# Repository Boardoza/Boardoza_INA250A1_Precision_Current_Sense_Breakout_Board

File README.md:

# Boardoza INA250A1 High Precision Current Sense Breakout Board

The **Boardoza INA250A1** is a high-precision **current-sense breakout board** based on the **Texas Instruments INA250A1** integrated current shunt monitor. It combines a precision differential amplifier and an internal **2 mΩ shunt resistor**, enabling accurate current measurements with minimal external components.

This breakout board is suitable for both **unidirectional and bidirectional current sensing** applications. Making it ideal for **power monitoring, energy management, motor control, battery systems, and industrial applications** where accurate current measurement is critical.

## [Click here to purchase!](https://www.ozdisan.com/ureticiler/boardoza)
| Front Side | Back Side |
|:---:|:---:|
|  |  |

---

## Key Features

- **High-Precision Current Shunt Monitor:** Enables accurate current measurement.  
- **Integrated 2 mΩ Precision Shunt Resistor:** Eliminates the need for an external shunt resistor.
- **Bidirectional Measurement Support:** Supports both unidirectional and bidirectional current measurement.
- **Wide Supply Voltage Range:** Compatible with wide supply voltage levels (**2.7 Vdc to 36 Vdc**).   
- **Analog Voltage Output:** Allows easy interfacing with ADCs and microcontrollers.
- **Low Power Consumption:** Suitable for energy-efficient applications.
- **Adjustable Reference Voltage (REF):** Enables output offset adjustment for measurement flexibility.  
- **Maximum Input Current Capability:** Supports current measurement up to **15 A (max)**.  

---

## Technical Specifications

**Model:** INA250A1  
**Manufacturer:** Boardoza  
**Manufacturer IC:** Texas Instruments  
**Functions:** Precision current sensing  
**Supply Voltage:** 2.7 V – 36 V  
**Maximum Input Current:** 15 A (Max)  
**Shunt Resistance:** 2 mΩ (internal)  
**Gain:** 200 mV/A  
**Output Type:** Analog voltage  
**Measurement Type:** Unidirectional / Bidirectional  
**Operating Temperature:** -40 °C to +125 °C  
**Board Dimensions:** 40 mm × 40 mm

---

## Board Pinout

### **( J1 ) Signal Connector**

| Pin Number | Pin Name | Description |
| :---: | :---: | --- |
| 1 | VS | Device power supply (2.7 V – 36 V) |
| 2 | REF | Reference voltage input |
| 3 | OUT | Analog output voltage |
| 4 | GND | Ground |

### **( J2 ) Current Path Connector**

| Pin Number | Pin Name | Description |
| :---: | :---: | --- |
| 1 | IN+ | Current sense input (supply side) |
| 2 | IN- | Current sense input (load side) |

---

## Board Dimensions

---

## Step Files

[Boardoza INA250A1.step](./assets/INA250A1%20Step.step)

---

## Datasheet

[INA250 Datasheet.pdf](./assets/INA250A1%20Datasheet.pdf)

---

## Version History

- V1.0.0 – Initial Release

---

## Support

- If you have any questions or need support, please contact **<support@boardoza.com>**

---

## **License**

This repository contains both hardware and software components:

### **Hardware Design**

[![CC BY-SA 4.0][cc-by-sa-shield]][cc-by-sa]

All hardware design files are licensed under [Creative Commons Attribution-ShareAlike 4.0 International License][cc-by-sa].

[cc-by-sa]: http://creativecommons.org/licenses/by-sa/4.0/
[cc-by-sa-shield]: https://img.shields.io/badge/License-CC%20BY--SA%204.0-lightgrey.svg

### **Software/Firmware**

[![BSD-3-Clause][bsd-shield]][bsd]

All software and firmware are licensed under [BSD 3-Clause License][bsd].

[bsd]: https://opensource.org/licenses/BSD-3-Clause
[bsd-shield]: https://img.shields.io/badge/License-BSD%203--Clause-blue.svg

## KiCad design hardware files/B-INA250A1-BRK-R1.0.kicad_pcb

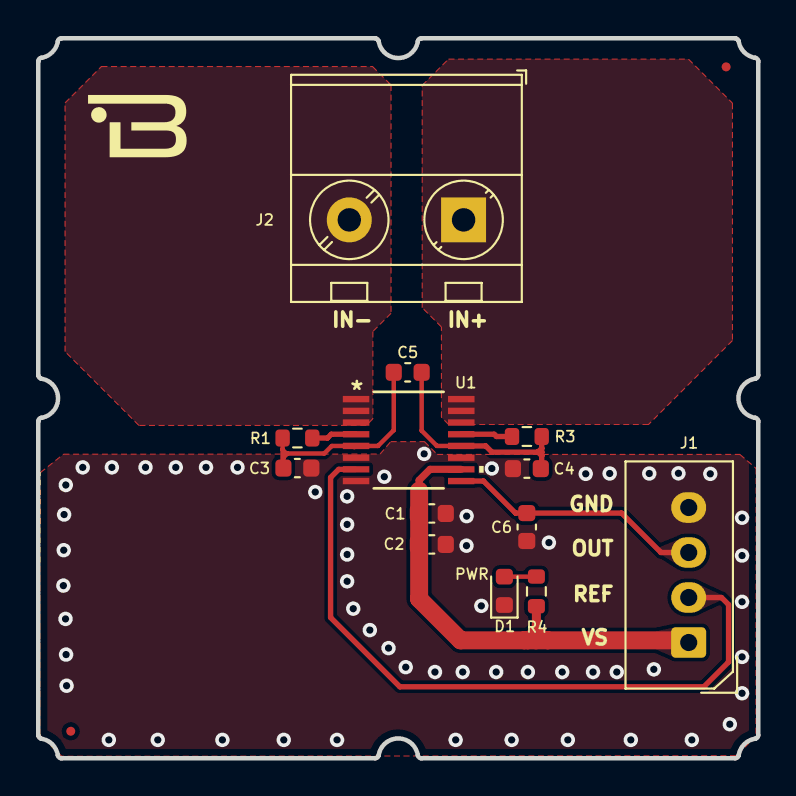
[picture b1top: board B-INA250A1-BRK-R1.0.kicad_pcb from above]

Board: 2 copper layers, 40.0 x 40.0 mm, 13 parts (0 on the bottom side), 11 nets.

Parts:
C1: 0,1uF; C_0603_1608Metric
C2: 1uF; C_0603_1608Metric
C3, C4, C5: 100nF; C_0603_1608Metric
C6: 10pF; C_0603_1608Metric
D1: LED; LED_0603_1608Metric
J1: Conn_01x04; 2317-04S_1x04_P2.50mm_Vertical
J2: Screw_Terminal_01x02; TerminalBlock_MetzConnect_Type701_RT11L02HGLU_1x02_P6.35mm_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
R1, R3: 0; R_0603_1608Metric
R4: 1k; R_0603_1608Metric
U1: INA250A1PWR; PW16_TEX

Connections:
/IN+: J2.1, U1.14 (IN+), U1.15 (IN+), U1.16 (IN+)
/IN-: J2.2, U1.1 (IN-), U1.2 (IN-), U1.3 (IN-)
/OUT: C6.2, J1.3, U1.9 (OUT)
/REF: J1.2, U1.7 (REF)
/SH+: R3.1, U1.13 (SH+)
/SH-: R1.1, U1.4 (SH-)
/VIN+: C4.2, C5.2, R3.2, U1.12 (VIN+)
/VIN-: C3.1, C5.1, R1.2, U1.5 (VIN-)
/VS: C1.2, C2.2, J1.1, R4.1, U1.10 (VS)
GND: C1.1, C2.1, C3.2, C4.1, C6.1, D1.1 (K), J1.4, U1.6 (GND), U1.8 (GND), U1.11 (GND)
unnamed: D1.2 (A), R4.2
